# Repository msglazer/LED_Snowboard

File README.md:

# LED_Snowboard
Wanted to add LED's to my new snowboard, controlled by GPS speed/board's angle

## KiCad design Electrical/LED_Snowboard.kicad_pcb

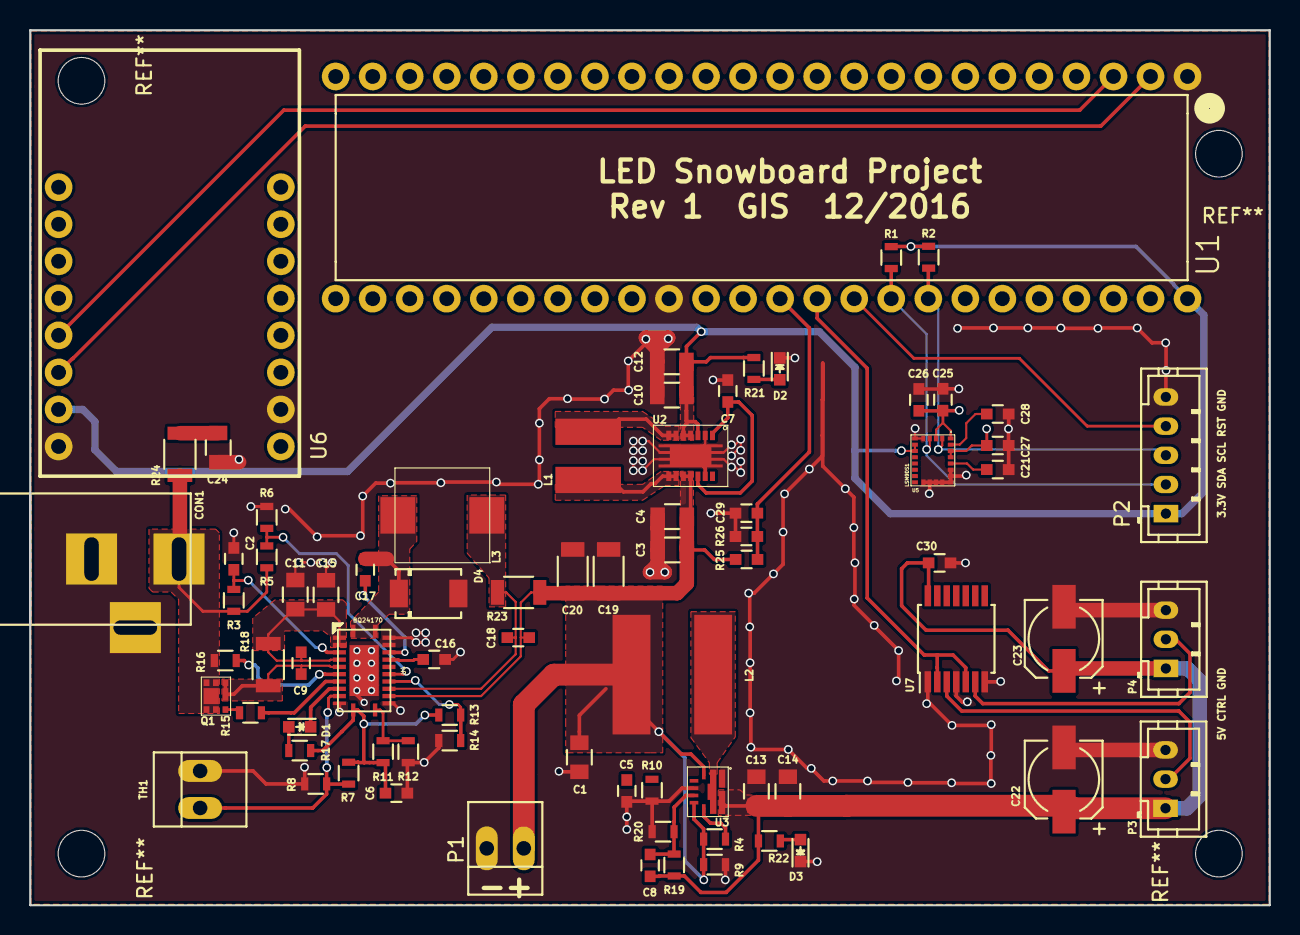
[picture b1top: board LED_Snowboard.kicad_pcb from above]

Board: 2 copper layers, 85.0 x 60.0 mm, 77 parts (0 on the bottom side), 43 nets.

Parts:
C1, C3, C4: 10uF; C_0805
C2, C6, C16, C29, C30: 1uF; C_0603
C5, C21: 10nF; C_0603
C7: 100nF; C_0603
C8: 10pF; C_0603
C9, C18, C26, C28: 0.1uF; C_0603
C10, C12, C13, C14: 22uF; C_0805
C11: 0.1uF; C_0805
C15: 4.7uF; C_0805
C17: 0.047uF; C_0603
C19, C20: 10uF; C_1206
C22, C23: 100uF; c_elec_5x5.3
C24: 2.2uF; C_0805
C25, C27: 10uF; C_0603
CON1: BARREL_JACK
D1, D2, D3: LED; LED_0603
D4: FSV530AF; DO-214AD
L1: 1.4uH; SDR0403-1R4ML
L2: 1uH; SRN8040-1R0Y
L3: 3.3uH; SRP7030-3R3FM
P1: CONN_01X02; PINHEAD1-2
P2: CONN_01X05; JST_PH_B5B-PH-K_05x2.00mm_Straight
P3, P4: CONN_01X03; JST_PH_B3B-PH-K_03x2.00mm_Straight
Q1: CSD17313Q2; WSON-FET-6
R1, R2: 4.7k; R_0603
R3: 10; R_0603
R4, R5, R9: 1M; R_0603
R6, R11, R13: 100K; R_0603
R7, R8: R; R_0603
R10: 30.9K; R_0603
R12: 32.4K; R_0603
R14: 13.7K; R_0603
R15, R16: 4.02K; R_0603
R17: 1.5K; R_0603
R18, R23: 10m; R_1206
R19: 619K; R_0603
R20: 205K; R_0603
R21: 260; R_0603
R22: 600; R_0603
R24: 2; R_1206
R25: 10K; C_0603
R26: 36K; C_0603
TH1: THERMISTOR; PINHEAD1-2
U1: Teensy_3.6; Teensy-3.6
U2: TPS63021; R-PVSON-N14
U3: TPS61236; VQFN-9
U4: BQ24170; pvqfn-n24
U5: LSM9DS1; LGA-24
U6: VenusGPS
U7: SN74AHCT125; TSSOP-14_4.4x5mm_Pitch0.65mm

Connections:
+3V3: C10.1, C12.1, C25.1, C26.1, C27.1, P2.1, R1.1, R2.1, R21.1, U1.48, U2.3, U2.4, U2.5, U5.1, U5.3, U5.7, U5.8, U5.22, U5.23, U6.7
+5V: C8.1, C13.1, C14.1, C22.1, C23.1, C30.1, P3.1, P4.1, R19.1, R22.1, U3.9, U7.14
/BAT: C1.1, C3.1, C4.1, C18.1, C19.2, C20.2, L2.1, P1.1, R4.2, R9.1, R23.1, R25.1, U2.10, U2.11, U3.3, U3.7, U4.15
/Connectors/LED_out1: P3.2, U7.3
/Connectors/LED_out2: P4.2, U7.6
/DISP_RST_Conn: P2.4, U1.39
/I2C_SCL_Conn: P2.3, R2.2, U1.41, U5.2
/I2C_SDA_Conn: P2.2, R1.2, U1.40, U5.4
/LED_CTRL_Conn: U1.38, U7.2, U7.5
/Microcontroller/BAT_MON: C29.1, R25.2, R26.1, U1.37
/Power Supply/AVCC: C2.1, R3.2, U4.4
/Power Supply/OVPSET: R5.2, R6.1, U4.18
/Power Supply/TS: R7.2, R8.1, TH1.1, U4.10
/Power Supply/VREF: C6.1, R7.1, R11.1, R13.1, R17.1, U4.12
/UART_RX_TX: U1.2, U6.6
/UART_TX_RX: U1.3, U6.5
/V_IN_Conn: CON1.1, Q1.1, R3.1, R5.1, R16.1, R24.1
GND: C1.2, C2.2, C3.2, C4.2, C5.2, C6.2, C7.2, C10.2, C11.2, C12.2, C13.2, C14.2, C15.1, C16.2, C19.1, C20.1, C21.2, C22.2, C23.2, C24.2, C25.2, C26.2, C27.2, C28.2, C29.2, C30.2, CON1.2, CON1.3, D2.1, D3.1, D4.2, P1.2, P2.5, P3.3, P4.3, R6.2, R8.2, R9.2, R10.2, R12.2, R14.2, R20.2, R26.2, TH1.2, U1.1, U1.34, U2.2, U2.13, U3.1, U3.5, U4.11, U4.14, U4.22, U4.23, U4.25, U5.5, U5.6, U5.14, U5.15, U5.16, U5.17, U5.18, U5.19, U5.20, U6.8, U6.10, U7.1, U7.4, U7.7
unnamed: C5.1, R10.1, U3.4
unnamed: C7.1, U2.1, U2.12
unnamed: C8.2, R19.2, R20.1, U3.6
unnamed: C9.2, Q1.3, R18.1, U4.6
unnamed: C9.1, C11.1, C15.2, R18.2, U4.2, U4.3, U4.5
unnamed: C16.1, U4.20
unnamed: C17.1, D4.1, L3.1, U4.1, U4.24
unnamed: C17.2, U4.21
unnamed: C18.2, L3.2, R23.2, U4.16
unnamed: C21.1, U5.21
unnamed: C24.1, R24.2
unnamed: C28.1, U5.24
unnamed: D1.1, U4.9
unnamed: D1.2, R17.2
unnamed: D2.2, R21.2
unnamed: D3.2, R22.2
unnamed: L1.1, U2.6, U2.7
unnamed: L1.2, U2.8, U2.9
unnamed: L2.2, U3.2
unnamed: Q1.2, R15.1
unnamed: R4.1, U3.8
unnamed: R11.2, R12.1, U4.13
unnamed: R13.2, R14.1, U4.17
unnamed: R15.2, U4.8
unnamed: R16.2, U4.7

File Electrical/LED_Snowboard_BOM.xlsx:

Bill of Materials (BOM) - LED Snowboard Project
Item # | Qty | Ref Des | Manufacturer | Mfg Part # | Dist. Part # | Price Per Unit | Total Price | Description | Package | Type | Datasheet |  |  |  |  |  | Notes
1 | 1 | U1 | PJRC |  |  | 0 | 0 | Teensy 3.6 |  | Through Hole
2 | 1 | U2 | Texas Instruments | TPS63021DSJR | 595-TPS63021DSJR | 2.74 | 2.74 | TPS63021 | PVSON-14 | SMD | http://www.ti.com/lit/gpn/tps63021
3 | 1 | U3 | Texas Instruments | TPS61236PRWLR | 595-TPS61236PRWLR | 2.0699999999999998 | 2.0699999999999998 | TPS61236 | VQFN-9 | SMD | http://www.ti.com/lit/ds/symlink/tps61236p.pdf
4 | 1 | U4 | Texas Instruments | BQ24170RGYR | 595-BQ24170RGYR | 4.05 | 4.05 | BQ24170 | VQFN-24 | SMD
5 | 1 | U5 | STMicro | LSM9DS1TR | 497-14946-1-ND | 6.4 | 6.4 | LSM9DS1 | LGA-24 | SMD | http://www.st.com/content/ccc/resource/technical/document/da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 |  |  |  |  |  | DIGIKEY
6 | 1 | U6 | Sparkfun |  |  | 0 | 0 | VenusGPS |  | Through Hole
7 | 1 | U7 | Texas Instruments | SN74AHCT125PWR | 595-SN74AHCT125PWR | 0.42 | 0.42 | 3.3V to 5V Level Shifter | TSSOP-14 | SMD | http://www.ti.com/lit/gpn/sn74ahct125
8 | 1 | Q1 | Texas Instruments | CSD17313Q2 | 595-CSD17313Q2 | 0.6 | 0.6 | NMOS Power MOSFET | WSON-FET-6 | SMD | http://www.ti.com/lit/gpn/csd17313q2
9 | 2 | R1,R2 | Vishay | CRCW06034K70FKEA | 71-CRCW0603-4.7K-E3 | 0.1 | 0.2 | 4.7k ohm Resistor | 0603 | SMD | http://www.mouser.com/ds/2/427/dcrcwe3-109170.pdf
10 | 1 | R3 | Ohmite | AS12J10R0ET | 588-AS12J10R0ET | 0.08 | 0.08 | 10 ohm Resistor | 1206 | SMD
11 | 3 | R4,R5,R9 | Yageo | RC0603FR-071ML | 603-RC0603FR-071ML | 0.1 | 0.30000000000000004 | 1M ohm Resistor | 0603 | SMD |  |  |  |  |  |  | Buy 10
12 | 3 | R6,R11,R13 | Vishay | CRCW0603100KFKEA | 71-CRCW0603-100K-E3 | 0.1 | 0.30000000000000004 | 100k ohm Resistor | 0603 | SMD | http://www.mouser.com/ds/2/427/dcrcwe3-109170.pdf |  |  |  |  |  | Buy 10
13 | 1 | R7 | Vishay | CRCW06035K23FKEA | 71-CRCW0603-5.23K-E3 | 0.1 | 0.1 | 5.23K ohm Resistor | 0603 | SMD |  |  |  |  |  |  | Buy 10
14 | 1 | R8 | Bourns | CR0603-FX-3012ELF | 652-CR0603FX-3012ELF | 0.1 | 0.1 | 30.1K ohm Resistor | 0603 | SMD |  |  |  |  |  |  | Buy 10
15 | 1 | R10 | Yageo | RC0603FR-0730K9L | 603-RC0603FR-0730K9L | 0.1 | 0.1 | 30.9K ohm Resistor | 0603 | SMD |  |  |  |  |  |  | Buy 10
16 | 1 | R12 | KOA Speer | RK73H1JTTD3242F | 660-RK73H1JTTD3242F | 0.1 | 0.1 | 32.4K ohm Resistor | 0603 | SMD
17 | 1 | R14 | Vishay | CRCW060313K7FKEA | 71-CRCW0603-13.7K-E3 | 0.1 | 0.1 | 13.7K ohm Resistor | 0603 | SMD |  |  |  |  |  |  | Buy 10
18 | 2 | R15,R16 | Vishay | CRCW06034K02FKEA | 71-CRCW0603-4.02K-E3 | 0.1 | 0.2 | 4.02k ohm Resistor | 0603 | SMD |  |  |  |  |  |  | Buy 10
19 | 1 | R17 | Vishay | CRCW06031K50JNEA | 71-CRCW0603J-1.5K-E3 | 0.1 | 0.1 | 1.5k ohm Resistor | 0603 | SMD |  |  |  |  |  |  | Buy 10
20 | 2 | R18,R23 | TE Connectivity / CGS | 2176055-1 | 279-2176055-1 | 0.16 | 0.32 | 10m ohm Resistor | 1206 | SMD |  |  |  |  |  |  | Buy 10
21 | 1 | R19 | Vishay | CRCW0603619KFKEA | 71-CRCW0603-619K-E3 | 0.1 | 0.1 | 619k ohm Resistor | 0603 | SMD |  |  |  |  |  |  | Buy 10
22 | 1 | R20 | Yageo | RC0603FR-07205KL | 603-RC0603FR-07205KL | 0.1 | 0.1 | 205k ohm Resistor | 0603 | SMD |  |  |  |  |  |  | Buy 10
23 | 1 | R21 | Vishay | CRCW0603261RFKEA | 71-CRCW0603-261-E3 | 0.1 | 0.1 | 260 ohm Resistor | 0603 | SMD |  |  |  |  |  |  | Buy 10
24 | 1 | R22 | Vishay | CRCW0603604RFKEA | 71-CRCW0603-604-E3 | 0.1 | 0.1 | 600 ohm Resistor | 0603 | SMD |  |  |  |  |  |  | Buy 10
25 | 1 | R24 | Panasonic | ERJ-8GEYJ2R0V | 667-ERJ-8GEYJ2R0V | 0.1 | 0.1 | 2 ohm Resistor | 1206 | SMD |  |  |  |  |  |  | Buy 10
26 | 1 | R25 | Vishay | CRCW060310K0FKEA | 71-CRCW0603-10K-E3 | 0.1 | 0.1 | 10k ohm Resistor | 0603 | SMD |  |  |  |  |  |  | Buy 10
27 | 1 | R26 | Vishay | CRCW060336K0FKEA | 71-CRCW0603-36K-E3 | 0.1 | 0.1 | 36k ohm Resistor | 0603 | SMD
28 | 3 | C1,C3,C4 | Murata Electronics | GRM21BR61A106KE19L | 81-GRM21BR61A106KE19 | 0.1 | 0.30000000000000004 | 10uF Capacitor | 0805 | SMD |  |  |  |  |  |  | Buy 10
29 | 5 | C2,C6,C16,C29,C30 | Murata Electronics | GRM188R61E105KA12D | 81-GRM188R61E105KA12 | 0.1 | 0.5 | 1uF Capacitor | 0603 | SMD |  |  |  |  |  |  | Buy 10
30 | 2 | C5,C21 | Wurth Electronics | 885012206040 | 710-885012206040 | 0.04 | 0.08 | 10nF Capacitor | 0603 | SMD
31 | 1 | C7 | AVX | 06033C104K4T2A | 581-06033C104K4 | 0.04 | 0.04 | 100nF Capacitor | 0603 | SMD
32 | 1 | C8 | Vishay / Vitramon | VJ0603A100JXACW1BC | 77-VJ0603A100JXACBC | 0.06 | 0.06 | 10pF Capacitor | 0603 | SMD
33 | 4 | C9,C18,C26,C28 | AVX | 06033C104K4T2A | 581-06033C104K4 | 0.08 | 0.32 | 0.1uF Capacitor | 0603 | SMD
34 | 4 | C10,C12,C13,C14 | AVX | 0805ZD226KAT2A | 581-0805ZD226KAT2A | 0.2 | 0.8 | 22uF Capacitor | 0805 | SMD
35 | 1 | C11 | Wurth Electronics | 885012207072 | 710-885012207072 | 7.0000000000000007E-2 | 7.0000000000000007E-2 | 0.1uF Capacitor | 0805 | SMD
36 | 1 | C15 | Vishay / Vitramon | VJ0805V475MXQTW1BC | 77-VJ0805V475MXQTBC | 0.1 | 0.1 | 4.7uF Capacitor | 0805 | SMD
37 | 1 | C17 | Wurth Electronics | 885012206044 | 710-885012206044 | 0.05 | 0.05 | 0.047uF Capacitor | 0603 | SMD
38 | 2 | C19,C20 | Vishay / Vitramon | VJ1206V106ZXQTW1BC | 77-VJ1206V106ZXQTBC | 0.1 | 0.2 | 10uF Capacitor | 1206 | SMD
39 | 1 | C24 | Vishay / Vitramon | VJ0805V225MXJTW1BC | 77-VJ0805V225MXJTBC | 0.1 | 0.1 | 2.2uF Capacitor | 0805 | SMD
40 | 2 | C25,C27 | Murata Electronics | GRM188C80G106ME47D | 81-GRM188C80G106ME7D | 0.13 | 0.26 | 10uF Capacitor | 0603 | SMD
41 | 2 | C22,C23 | Panasonic | EEE-1AA101WR | 667-EEE-1AA101WR | 0.33 | 0.66 | 100uF Electrolytic Capacitor | 5mm x 5.5mm | SMD | http://www.mouser.com/ds/2/315/ABA0000C1145-947633.pdf
42 | 1 | TH1 | Semitec | 103AT-2 | 954-103AT-2 | 2.25 | 2.25 | 103AT Thermistor |  | Through Hole | http://www.mouser.com/ds/2/362/semitec_atthermistor-371460.pdf
43 | 1 | L1 | Bourns | SDR0403-1R4ML | 652-SDR0403-1R4ML | 0.47 | 0.47 | 3.3V Regulator 1.4uH Inductor | 4.5mm x 4.5mm | SMD | http://www.mouser.com/ds/2/54/dr0403-778115.pdf
44 | 1 | L2 | Bourns | SRN8040-1R0Y | 652-SRN8040-1R0Y | 0.57999999999999996 | 0.57999999999999996 | 5V Regulator 1uH Inductor | 8mm x 8mm | SMD | http://www.mouser.com/ds/2/54/RN8040-778099.pdf
45 | 1 | L3 | Bourns | SRP7030-3R3FM | 652-SRP7030-3R3FM | 1.18 | 1.18 | Battery Charger 3.3uH Inductor | 6.5mm x 6.5mm | SMD | http://www.mouser.com/ds/2/54/SRP7030F-76916.pdf
46 | 3 | D1,D2,D3 | Kingbright | AP1608SGC | 604-AP1608SGC | 0.13 | 0.39 | Green LED | 0603 | SMD | http://www.mouser.com/ds/2/216/AP1608SGC-29521.pdf
47 | 1 | D4 | Fairchild Semiconductor | FSV530AF | 512-FSV530AF | 0.46 | 0.46 | Charging Circuit Diode | DO-214-2 | SMD | http://www.mouser.com/ds/2/149/FSV530AF-607397.pdf
48 | 1 | PCB | OSHPark |  |  | 13.233333333333334 | 13.233333333333334 | Circuit Board (3 boards) |  | Mixed
 |  |  |  |  | Board Multiplier: | 1 | BOM Total:
 |  |  |  |  |  |  | 27.850000000000019
 |  |  |  |  |  |  | PCB Total:
 |  |  |  |  |  |  | 13.233333333333334
 |  |  |  |  |  |  | Grand Total:
 |  |  |  |  |  |  | 41.083333333333357

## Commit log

2016-12-03 :circus_tent: Added .gitattributes & .gitignore files
2016-12-03 And so it begins!
    Schematic started, picking out parts
2016-12-07 Continued work on schematic
    There's actually some schematics in the project now! Power is 90% done,
    fleshing out everything else as well
2016-12-19 Finished sensor sheet
2016-12-19 Finished power sheet
2016-12-19 almost finished with MCU sheet
2016-12-19 Continued work on schematic
2016-12-21 creating parts
2016-12-21 schematic 95% donbe
2016-12-21 schematic 95% done
2016-12-21 started PCB
2016-12-23 Parts!
2016-12-23 Added BOM
2016-12-23 Software "started"
2016-12-23 minor tweaks
2016-12-23 PCB work continuing, all footprints finished
2016-12-24 PCB 90% done
2016-12-24 Generated Gerber files
2016-12-24 I downloaded some libraries
2016-12-24 Finished PCB
2017-01-03 working on the software
2017-01-03 Finished BOM
2017-01-03 Minor Changes
2017-01-07 Working on software
2017-01-08 Continued work on software
2017-01-09 working on box to hold everything
2017-01-30 CAD stuff
2017-04-04 really minor commit to keep everything together
